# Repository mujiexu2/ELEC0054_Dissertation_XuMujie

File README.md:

# Bespoke Wearable IMU Device
This wearable system aims to be cost-effective, lightweight and compact size.
This project is separated in two sections done in parallel, prototyping and PCB Design. The STM32 board programming is 
done in STM32CubeIDE, schematics done in KiCad, PCB done in DipTrace, API run in Python(Vscode).

For communication, we have used SPI protocol in MCU & IMU communication, QSPI protocol in Memory & MCU communication, 
USB transmission in Board & PC communication.

STML412CBT6 communicates with ICM-20948 with SPI, communicates with the Memory module with
QSPI, USB interface designed on board is responsible for transmit data to the PC and
present on the API.

Due to time constraints, the PCB file has not been updated to match the version of the schematics file.
The PCB board has been tested to have the low power characteristics, with 0.121W. Using YOJOCK USB C Tester Power Meter.

## Prototype
- NUCLEO-L412RB-P (STM32 Nucleo-64 development board with STM32L412RB MCU, SMPS, supports Arduino, ST Morpho connectivity)
- SparkFun 9DoF IMU (ICM-20948) Breakout Board
- MT25QL512ABB-based self-made Flash Memory Breakout Board
- Adafruit USB Micro-B Breakout Board

## PCB Design (size: 50.961mm x 43.929mm)
Component List:
- InvenSense ICM20948 (World's Lowest-Power 9‑Axis MEMS MotionTracking® Device)
- STM32L412CBT6 (Ultra-low-power Arm® Cortex®-M4 32-bit MCU+FPU)
- MT25QL512ABB (Serial NOR Flash Memory)
- USB Connector, Micro USB Type B

## Component List:

## File Description
### ICM_SPI_rtc(STM32CubeIDE programs):
- icm20948.c: Read accelerometer(unit: g), gyroscope(units: dps) and magnetometer(units: uT) data
- time.c: Get UTC time, current local UK time, elapsed time
- main.c: Combined time data and sensor data, and sent to USB VCP for future analysis

#### STM32CubeIDE SPI configuration

#### STM32CubeIDE USB + USB Device configuration

#### STM32CubeIDE RTC configuration

### PCB(DipTrace files):
- PCB-Xu Mujie-0614.dip: The PCB Diptrace file for assembled PCB board

- PCB-Xu Mujie-spi-0815.dip: The newest PCB Diptrace file

### python API(python .py/.ipynb)
- time.c/time.ipynb:
  - receive data(time and sensor data) transmitted from the USB VCP
  - split data and save as .csv file in local directory
  - The csv file stored in the format:

### schematics(KiCad file)
- 1_nrst.kicad_sch: circuits schematic up to date version

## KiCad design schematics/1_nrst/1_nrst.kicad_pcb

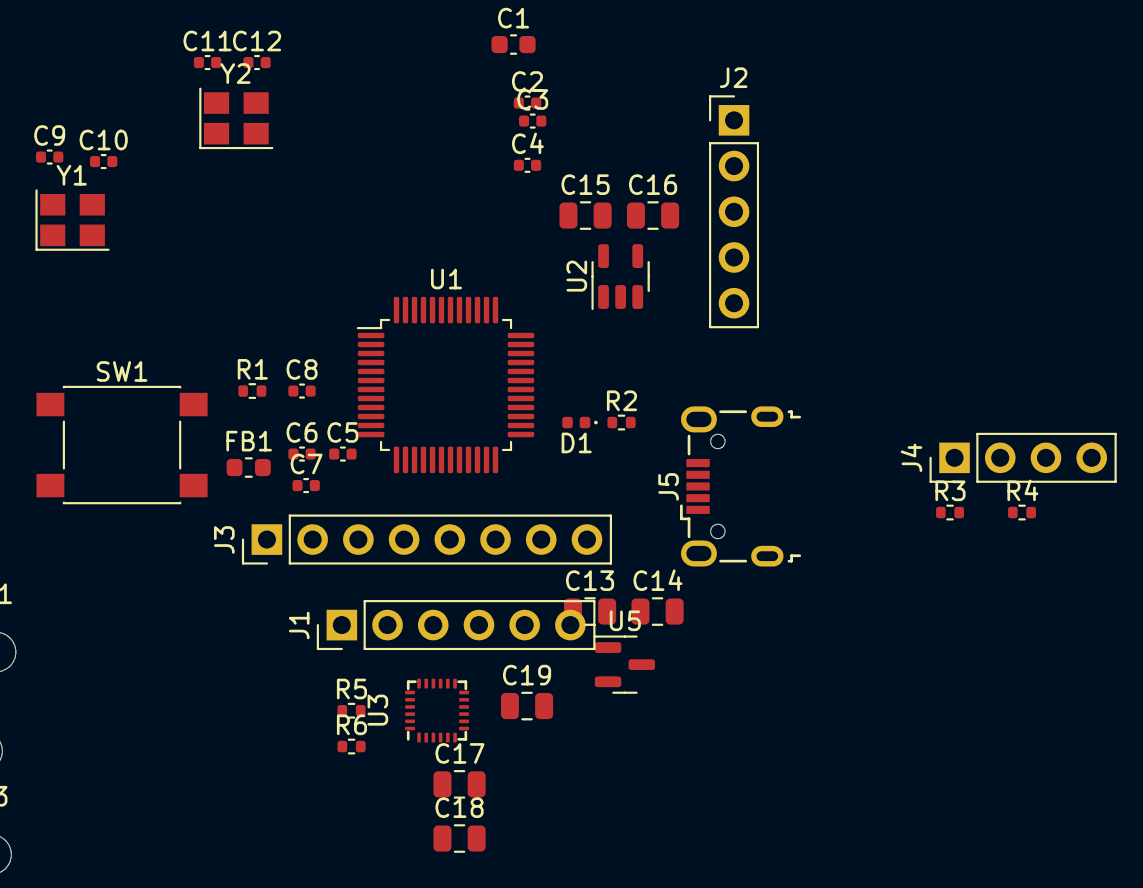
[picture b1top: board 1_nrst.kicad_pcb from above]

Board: 2 copper layers, 43 parts (0 on the bottom side), 31 nets, no tracks yet.

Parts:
C1: 10u; C_0603_1608Metric
C2, C3, C4, C8: 100n; C_0402_1005Metric
C5: 10n; C_0402_1005Metric
C6, C7: 1u; C_0402_1005Metric
C9, C10: 10p; C_0402_1005Metric
C11, C12: 15p; C_0402_1005Metric
C13, C14, C15, C16: 1uF; C_0805_2012Metric
C17, C18, C19: 0.1uF; C_0805_2012Metric
D1: RED; LED_0402_1005Metric
FB1: 120R; L_0603_1608Metric
H1, H2, H3, H4: MountingHole; MountingHole_2.2mm_M2
J1: Conn_01x06_Pin; PinHeader_1x06_P2.54mm_Vertical
J2: Conn_01x05_Pin; PinHeader_1x05_P2.54mm_Vertical
J3: Conn_01x08_Pin; PinHeader_1x08_P2.54mm_Vertical
J4: Conn_01x04_Pin; PinHeader_1x04_P2.54mm_Vertical
J5: USB_B_Micro; USB_Micro-B_Wuerth_629105150521
R1, R5, R6: 10k; R_0402_1005Metric
R2, R3, R4: 4k7; R_0402_1005Metric
SW1: SW_SPST; SW_SPST_PTS645
U1: STM32L412CBT6; LQFP-48_7x7mm_P0.5mm
U2: MIC5504-3.3YM5; SOT-23-5
U3: ICM-20948; InvenSense_QFN-24_3x3mm_P0.4mm
U5: MCP1703AT-1802E/TT; SOT-23
Y1: 48MHz; Crystal_SMD_3225-4Pin_3.2x2.5mm
Y2: 32.786kHz; Crystal_SMD_3225-4Pin_3.2x2.5mm

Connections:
+1V8: C14.1, C17.1, C18.1, R5.1, U3.8 (VDDIO), U3.13 (VDD), U5.2 (VO)
+3.3V: C1.1, C2.1, C3.1, C4.1, C7.1, C13.1, C16.1, FB1.2, J1.1, J2.5, J3.1, J4.1, R1.1, R3.1, R4.1, U1.1 (VBAT), U1.24 (VDD), U1.36 (VDDUSB), U1.48 (VDD), U2.5 (VOUT), U5.3 (VI)
+3.3VA: C5.1, C6.1, FB1.1, U1.9 (VDDA)
/RESET: C8.1, R1.2, SW1.2 (B), U1.7 (NRST)
/SWCLK: J2.3, U1.37 (PA14)
/SWDIO: J2.4, U1.34 (PA13)
/USB_D+: J5.3 (D+), U1.33 (PA12)
/USB_D-: J5.2 (D-), U1.32 (PA11)
GND: C1.2, C2.2, C3.2, C4.2, C5.2, C6.2, C7.2, C8.2, C9.2, C10.2, C11.2, C12.2, C13.2, C14.2, C15.2, C16.2, C17.2, C18.2, C19.1, J1.6, J2.1, J3.8, J4.4, J5.5 (GND), R2.2, R6.1, SW1.1 (A), U1.8 (VSSA), U1.23 (VSS), U1.35 (VSS), U1.47 (VSS), U2.2 (GND), U3.18 (GND), U3.20 (GND), U5.1 (GND), Y1.2, Y1.4, Y2.2, Y2.4
HSE_IN: C9.1, U1.5 (PH0), Y1.1
HSE_OUT: C10.1, U1.6 (PH1), Y1.3
I2C1_SCL: J4.2, R3.2, U1.30 (PA9)
I2C1_SDA: J4.3, R4.2, U1.31 (PA10)
LED_STATUS: D1.2 (A), U1.26 (PB13)
LSE_IN: C11.1, U1.3 (PC14), Y2.1
LSE_OUT: C12.1, U1.4 (PC15), Y2.3
unnamed: D1.1 (K), R2.1
unnamed: R6.2, U3.11 (FSYNC)
unnamed: C19.2, U3.10 (REGOUT)
QSPI_CLK: J3.3, U1.13 (PA3)
QSPI_IO0: J3.4, U1.19 (PB1)
QSPI_IO1: J3.5, U1.18 (PB0)
QSPI_IO2: J3.6, U1.17 (PA7)
QSPI_IO3: J3.7, U1.16 (PA6)
QSPI_NCS: J3.2, U1.12 (PA2)
SPI_MISO: J1.5, U1.40 (PB4), U3.9 (SDO/AD0)
SPI_MOSI: J1.4, U1.41 (PB5), U3.24 (SDA/SDI)
SPI_NCS: J1.2, R5.2, U1.14 (PA4), U3.22 (~CS)
SPI_SCK: J1.3, U1.15 (PA5), U3.23 (SCL/SCLK)
SWO: J2.2, U1.39 (PB3)
VBUS: C15.1, J5.1 (VBUS), U2.1 (VIN), U2.3 (EN)

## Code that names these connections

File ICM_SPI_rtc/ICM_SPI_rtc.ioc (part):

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Mcu.Name=STM32L412RBTxP
Mcu.Package=LQFP64
Mcu.UserName=STM32L412RBTxP
PA10.Mode=I2C
PA10.Signal=I2C1_SDA
PA11.Mode=Device
PA11.Signal=USB_DM
PA12.Mode=Device
PA12.Signal=USB_DP
PA13\ (JTMS/SWDIO).Mode=Trace_Asynchronous_SW
PA13\ (JTMS/SWDIO).Signal=SYS_JTMS-SWDIO
PA14\ (JTCK/SWCLK).Mode=Trace_Asynchronous_SW
PA14\ (JTCK/SWCLK).Signal=SYS_JTCK-SWCLK
PA4.GPIOParameters=GPIO_Speed,PinState,GPIO_Label
PA4.GPIO_Label=SPI1_CS
PA4.GPIO_Speed=GPIO_SPEED_FREQ_HIGH
PA4.PinState=GPIO_PIN_SET
PA4.Signal=GPIO_Output
PA5.Mode=Full_Duplex_Master
PA5.Signal=SPI1_SCK
PA9.Mode=I2C
PA9.Signal=I2C1_SCL
PB13.GPIOParameters=PinState,GPIO_Label
PB13.GPIO_Label=LED
PB13.PinState=GPIO_PIN_SET
PB13.Signal=GPIO_Output
PB3\ (JTDO/TRACESWO).Mode=Trace_Asynchronous_SW
PB3\ (JTDO/TRACESWO).Signal=SYS_JTDO-SWO
PB4\ (NJTRST).Mode=Full_Duplex_Master
PB4\ (NJTRST).Signal=SPI1_MISO
PB5.Mode=Full_Duplex_Master
PB5.Signal=SPI1_MOSI
PC14-OSC32_IN\ (PC14).Mode=LSE-External-Oscillator
PC14-OSC32_IN\ (PC14).Signal=RCC_OSC32_IN
PC15-OSC32_OUT\ (PC15).Mode=LSE-External-Oscillator
PC15-OSC32_OUT\ (PC15).Signal=RCC_OSC32_OUT
PH0-OSC_IN\ (PH0).Mode=HSE-External-Oscillator
PH0-OSC_IN\ (PH0).Signal=RCC_OSC_IN
PH1-OSC_OUT\ (PH1).Mode=HSE-External-Oscillator
PH1-OSC_OUT\ (PH1).Signal=RCC_OSC_OUT
RCC.HSE_VALUE=8000000
RCC.SYSCLKFreq_VALUE=80000000
RCC.SYSCLKSource=RCC_SYSCLKSOURCE_PLLCLK
board=custom

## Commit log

2023-09-05 initial commmit: update STM32CubeIDE files
2023-09-05 schematic updated
2023-09-05 PCB updated
2023-09-05 comments prepared for STM32CubeIDE files
2023-09-05 update python API
2023-09-06 readme updated
2023-09-06 images updated
2023-09-06 readme finished
2023-09-06 finished
